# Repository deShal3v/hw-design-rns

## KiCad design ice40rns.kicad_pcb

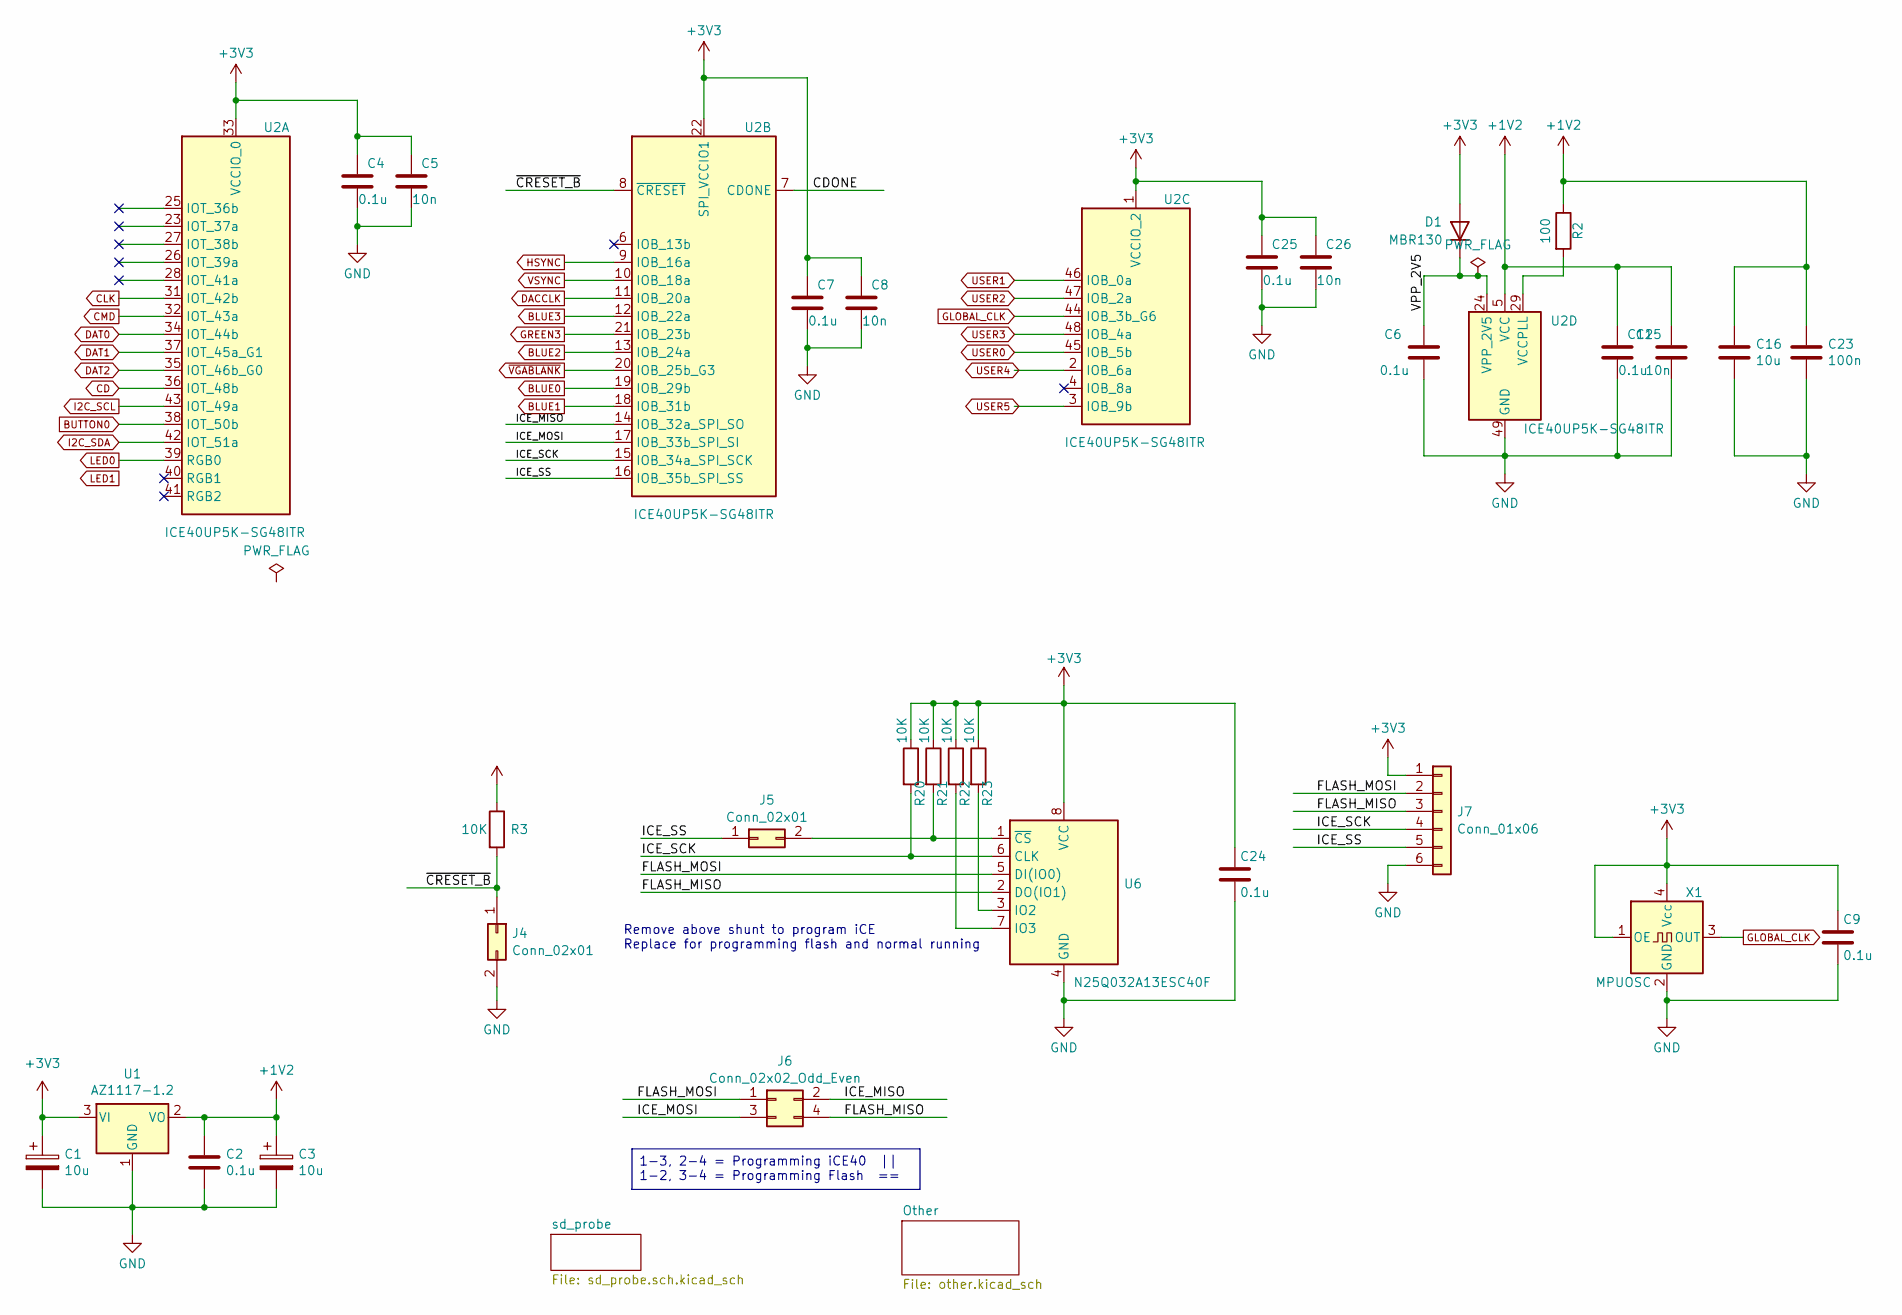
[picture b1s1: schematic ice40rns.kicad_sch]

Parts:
C1, C3: 10u; CP_EIA-3216-10_Kemet-I
C2, C4, C6, C7, C9, C12, C24, C25: 0.1u; C_0805_2012Metric
C5, C8, C15, C26: 10n; C_0805_2012Metric
C16: 10u; C_0805_2012Metric
C23: 100n; C_0805_2012Metric
D1: MBR130; D_SOD-123
J4, J5: Conn_02x01; PinHeader_2x01_P2.54mm_Vertical
J6: Conn_02x02_Odd_Even; PinHeader_2x02_P2.54mm_Vertical
J7: Conn_01x06; PinHeader_1x06_P2.54mm_Vertical
R2: 100; R_0805_2012Metric
R3, R20, R21, R22, R23: 10K; R_0805_2012Metric
U1: AZ1117-1.2; SOT-223-3_TabPin2
U2: ICE40UP5K-SG48ITR; QFN-48-1EP_7x7mm_P0.5mm_EP5.6x5.6mm
U6: N25Q032A13ESC40F; SOP-8_3.9x4.9mm_P1.27mm
X1: MPUOSC; Oscillator_SMD_SeikoEpson_SG8002LB-4Pin_5.0x3.2mm

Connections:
+1V2: C2.1, C3.1, C12.1, C15.1, C16.1, C23.1, R2.1, U1.2 (VO), U2.5 (VCC), U2.30 (VCC)
+3V3: C1.1, C4.1, C5.1, C7.1, C8.1, C9.1, C24.1, C25.1, C26.1, D1.2 (A), J7.1, R3.1, R20.1, R21.1, R22.1, R23.1, U1.3 (VI), U2.1 (VCCIO_2), U2.22 (SPI_VCCIO1), U2.33 (VCCIO_0), U6.8 (VCC), X1.1 (OE), X1.4 (Vcc); also elsewhere on the board
/CDONE: U2.7 (CDONE)
/FLASH_MISO: J6.4, J7.3, U6.2 (DO(IO1))
/FLASH_MOSI: J6.1, J7.2, U6.5 (DI(IO0))
/ICE_MISO: J6.2, U2.14 (IOB_32a_SPI_SO)
/ICE_MOSI: J6.3, U2.17 (IOB_33b_SPI_SI)
/ICE_SCK: J7.4, R20.2, U2.15 (IOB_34a_SPI_SCK), U6.6 (CLK)
/ICE_SS: J5.1, J7.5, U2.16 (IOB_35b_SPI_SS)
/VPP_2V5: C6.1, D1.1 (K), U2.24 (VPP_2V5)
/~CRESET_B: J4.1, R3.2, U2.8 (~CRESET)
BLUE0: U2.19 (IOB_29b)
BLUE1: U2.18 (IOB_31b)
BLUE2: U2.13 (IOB_24a)
BLUE3: U2.12 (IOB_22a)
BUTTON0: U2.38 (IOT_50b)
CD: U2.36 (IOT_48b); also elsewhere on the board
CLK: U2.31 (IOT_42b); also elsewhere on the board
CMD: U2.32 (IOT_43a); also elsewhere on the board
DACCLK: U2.11 (IOB_20a)
DAT0: U2.34 (IOT_44b); also elsewhere on the board
DAT1: U2.37 (IOT_45a_G1); also elsewhere on the board
DAT2: U2.35 (IOT_46b_G0); also elsewhere on the board
GLOBAL_CLK: U2.44 (IOB_3b_G6), X1.3 (OUT)
GND: C1.2, C2.2, C3.2, C4.2, C5.2, C6.2, C7.2, C8.2, C9.2, C12.2, C15.2, C16.2, C23.2, C24.2, C25.2, C26.2, J4.2, J7.6, U1.1 (GND), U2.49 (GND), U6.4 (GND), X1.2 (GND); also elsewhere on the board
GREEN3: U2.21 (IOB_23b)
HSYNC: U2.9 (IOB_16a)
I2C_SCL: U2.43 (IOT_49a); also elsewhere on the board
I2C_SDA: U2.42 (IOT_51a); also elsewhere on the board
LED0: U2.39 (RGB0); also elsewhere on the board
unnamed: J5.2, R21.2, U6.1 (~CS)
unnamed: R2.2, U2.29 (VCCPLL)
unnamed: R23.2, U6.3 (IO2)
unnamed: R22.2, U6.7 (IO3)
USER0: U2.45 (IOB_5b)
USER1: U2.46 (IOB_0a)
USER2: U2.47 (IOB_2a)
USER3: U2.48 (IOB_4a)
USER4: U2.2 (IOB_6a)
USER5: U2.3 (IOB_9b)
VSYNC: U2.10 (IOB_18a)
~VGABLANK: U2.20 (IOB_25b_G3)

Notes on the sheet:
Remove above shunt to program iCE Replace for programming flash and normal running
1-3, 2-4 = Programming iCE40 || 1-2, 3-4 = Programming Flash ==

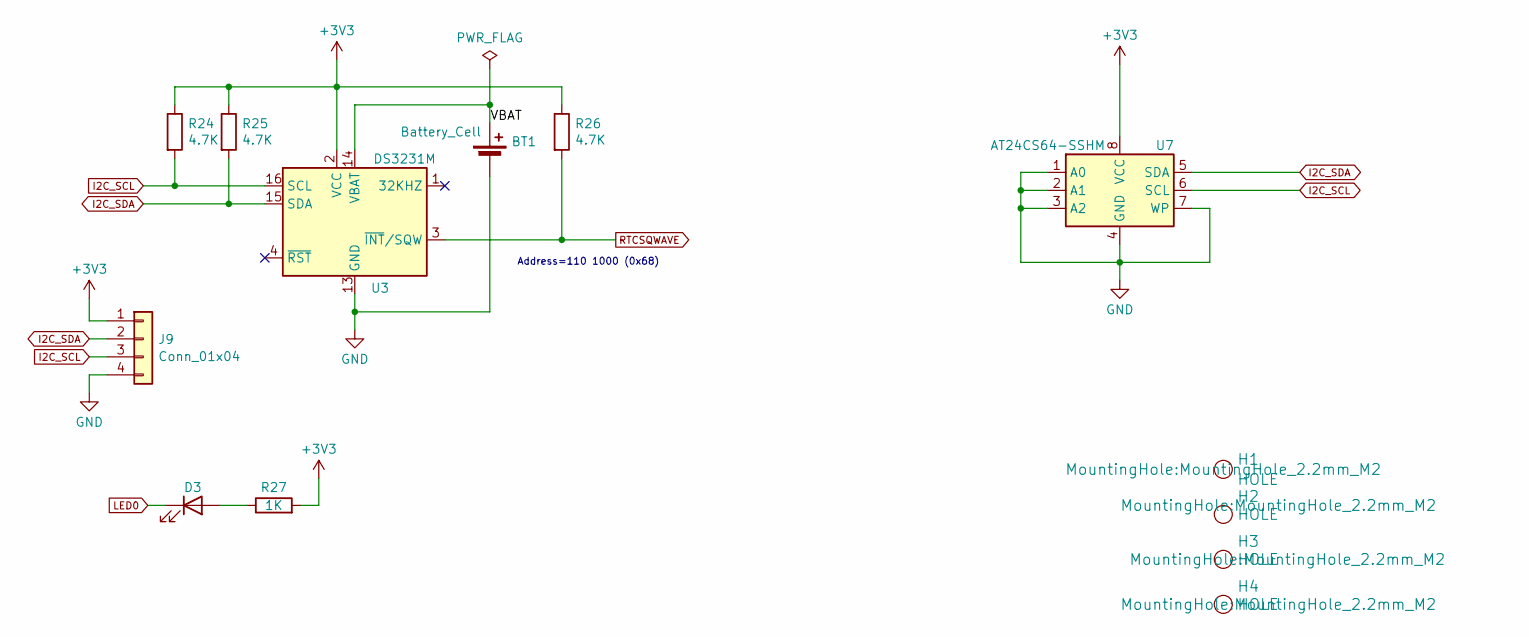
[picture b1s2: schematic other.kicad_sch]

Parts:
BT1: Battery_Cell; BatteryHolder_Keystone_3000_1x12mm
D3: CDONE_LED; LED_1210_3225Metric
H1, H2, H3, H4: HOLE; MountingHole_2.2mm_M2
J9: Conn_01x04; PinHeader_1x04_P2.54mm_Vertical
R24, R25, R26: 4.7K; R_0805_2012Metric
R27: 1K; R_0805_2012Metric
U3: DS3231M; SOIC-16W_7.5x10.3mm_P1.27mm
U7: AT24CS64-SSHM; SOIC-8_3.9x4.9mm_P1.27mm

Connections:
+3V3: J9.1, R24.1, R25.1, R26.1, R27.2, U3.2 (VCC), U7.8 (VCC); also elsewhere on the board
/Other/VBAT: BT1.1 (+), U3.14 (VBAT)
GND: BT1.2 (-), J9.4, U3.5 (GND), U3.6 (GND), U3.7 (GND), U3.8 (GND), U3.9 (GND), U3.10 (GND), U3.11 (GND), U3.12 (GND), U3.13 (GND), U7.1 (A0), U7.2 (A1), U7.3 (A2), U7.4 (GND), U7.7 (WP); also elsewhere on the board
I2C_SCL: J9.3, R24.2, U3.16 (SCL), U7.6 (SCL); also elsewhere on the board
I2C_SDA: J9.2, R25.2, U3.15 (SDA), U7.5 (SDA); also elsewhere on the board
LED0: D3.1 (K); also elsewhere on the board
unnamed: D3.2 (A), R27.1
RTCSQWAVE: R26.2, U3.3 (~INT/SQW)

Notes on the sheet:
Address=110 1000 (0x68)

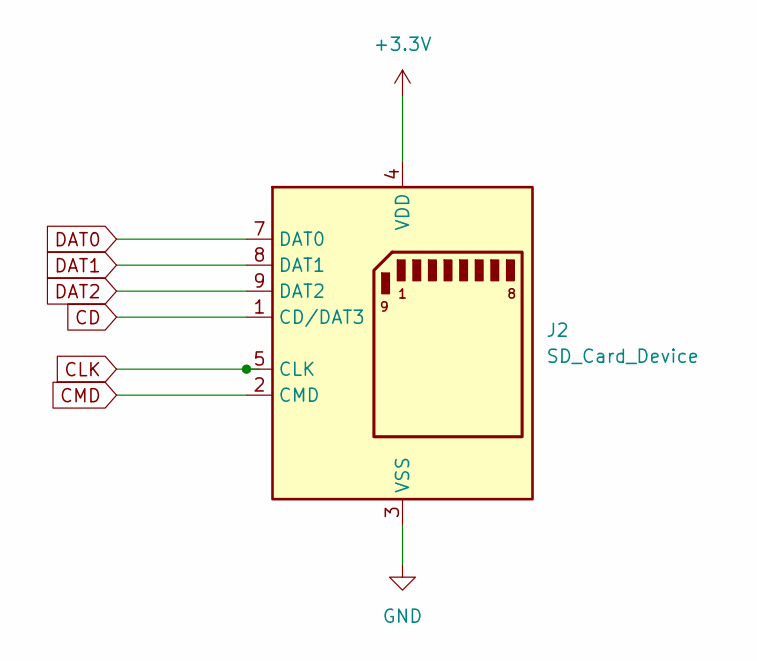
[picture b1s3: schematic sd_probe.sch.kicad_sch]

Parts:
J2: SD_Card_Device; SD_Card_Device_16mm_SlotDepth

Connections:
+3.3V: J2.4 (VDD)
CD: J2.1 (CD/DAT3); also elsewhere on the board
CLK: J2.5 (CLK); also elsewhere on the board
CMD: J2.2 (CMD); also elsewhere on the board
DAT0: J2.7 (DAT0); also elsewhere on the board
DAT1: J2.8 (DAT1); also elsewhere on the board
DAT2: J2.9 (DAT2); also elsewhere on the board
GND: J2.3 (VSS), J2.6 (VSS); also elsewhere on the board

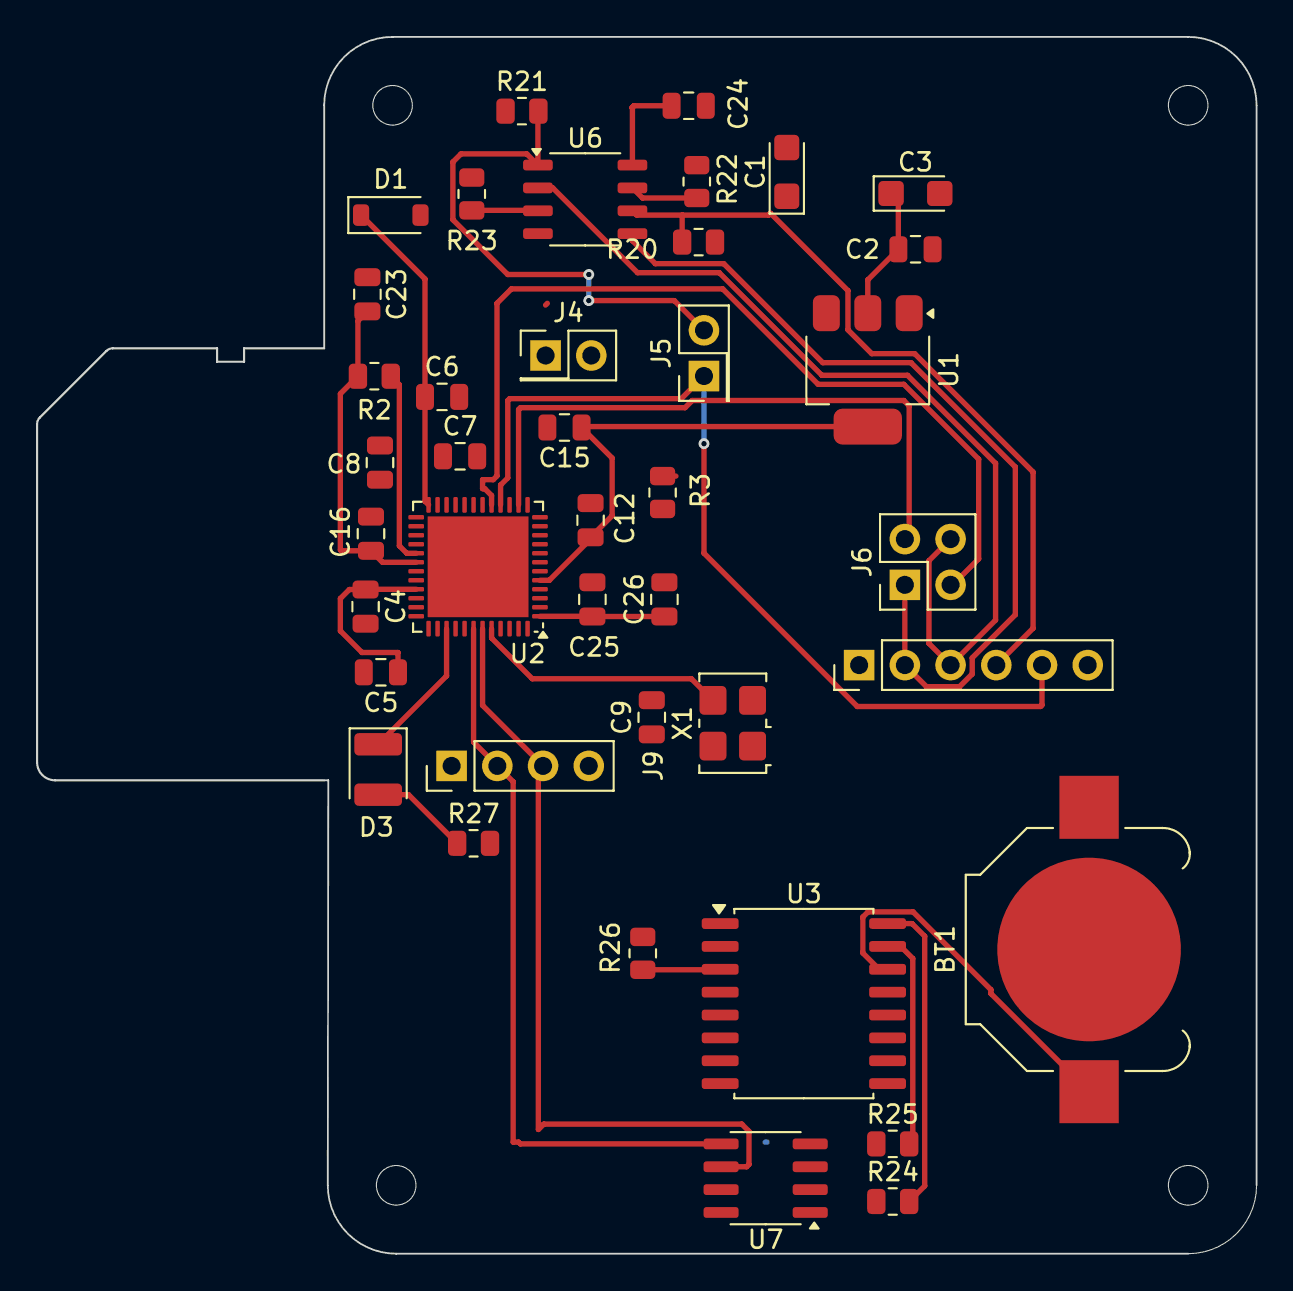
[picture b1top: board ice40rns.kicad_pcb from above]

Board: 2 copper layers, 67.7 x 67.6 mm, 45 parts (0 on the bottom side), 28 nets.

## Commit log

2025-08-17 hardware design files
